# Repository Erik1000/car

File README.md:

# Car

Controlling car functions remotely

This uses an old android phone as hub which connects via BLE to chips controlling functions such as:

- Ignition (remote start, assuming engine immobiliser reports OK)
- windows
- door lock

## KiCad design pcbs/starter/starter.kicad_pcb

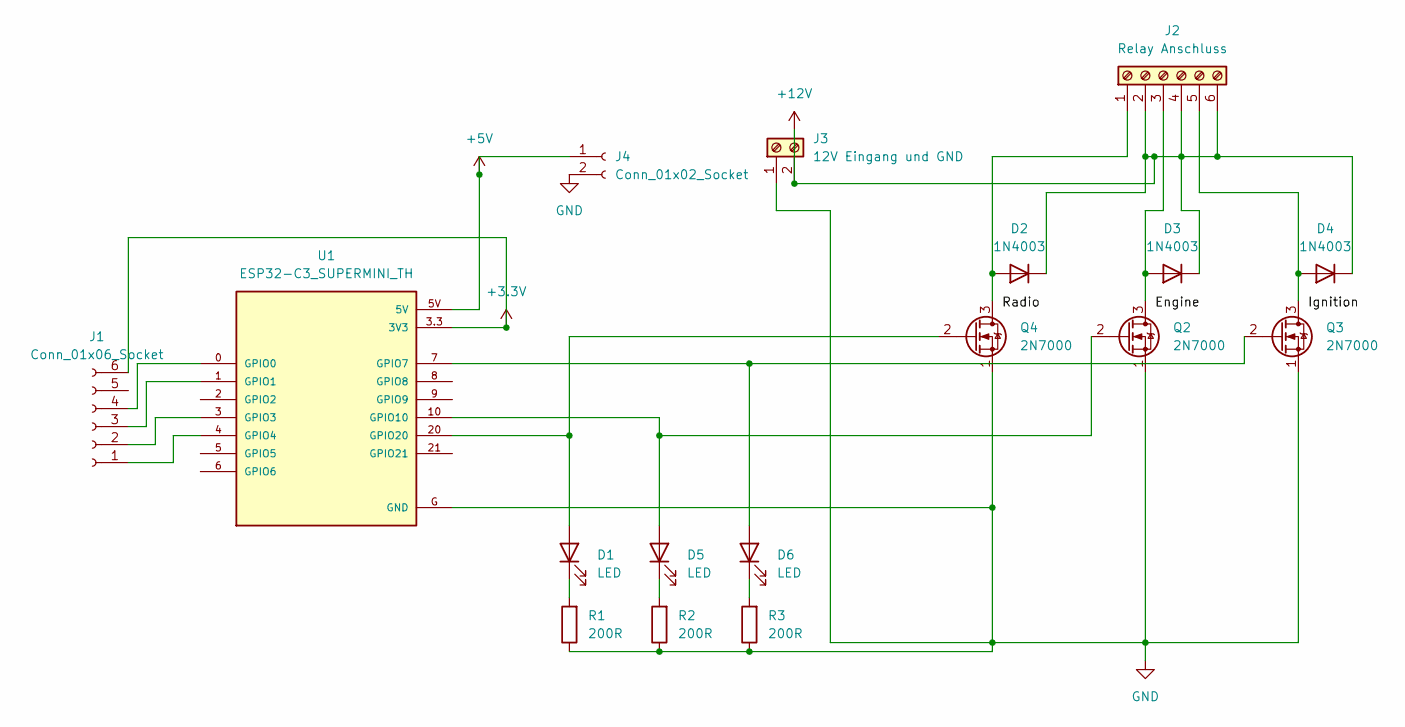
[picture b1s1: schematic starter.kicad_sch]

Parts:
D1, D5, D6: LED; LED_D5.0mm
D2, D3, D4: 1N4003; D_DO-41_SOD81_P10.16mm_Horizontal
J1: Conn_01x06_Socket; JST_XH_B6B-XH-AM_1x06_P2.50mm_Vertical
J2: Relay Anschluss; TerminalBlock_CUI_TB007-508-06_1x06_P5.08mm_Horizontal
J3: 12V Eingang und GND; TerminalBlock_CUI_TB007-508-02_1x02_P5.08mm_Horizontal
J4: Conn_01x02_Socket; JST_XH_B2B-XH-AM_1x02_P2.50mm_Vertical
Q2, Q3, Q4: 2N7000; TO-92_Inline
R1, R2, R3: 200R; R_Axial_DIN0204_L3.6mm_D1.6mm_P5.08mm_Horizontal
U1: ESP32-C3_SUPERMINI_TH; MODULE_ESP32-C3_SUPERMINI

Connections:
+3.3V: J1.6, U1.3.3 (3V3)
+5V: J4.1, U1.5V
+12V: D2.1 (K), D3.1 (K), D4.1 (K), J2.2, J2.4, J2.6, J3.2
GND: J3.1, J4.2, Q2.1 (S), Q3.1 (S), Q4.1 (S), R1.1, R2.1, R3.1, U1.G (GND)
unnamed: D1.2 (A), Q4.2 (G), U1.20 (GPIO20)
unnamed: D1.1 (K), R1.2
unnamed: D2.2 (A), J2.1, Q4.3 (D)
unnamed: D3.2 (A), J2.3, Q2.3 (D)
unnamed: D4.2 (A), J2.5, Q3.3 (D)
unnamed: D5.2 (A), Q2.2 (G), U1.10 (GPIO10)
unnamed: D5.1 (K), R2.2
unnamed: D6.2 (A), Q3.2 (G), U1.7 (GPIO7)
unnamed: D6.1 (K), R3.2
unnamed: J1.1, U1.4 (GPIO4)
unnamed: J1.2, U1.3 (GPIO3)
unnamed: J1.3, U1.1 (GPIO1)
unnamed: J1.4, U1.0 (GPIO0)

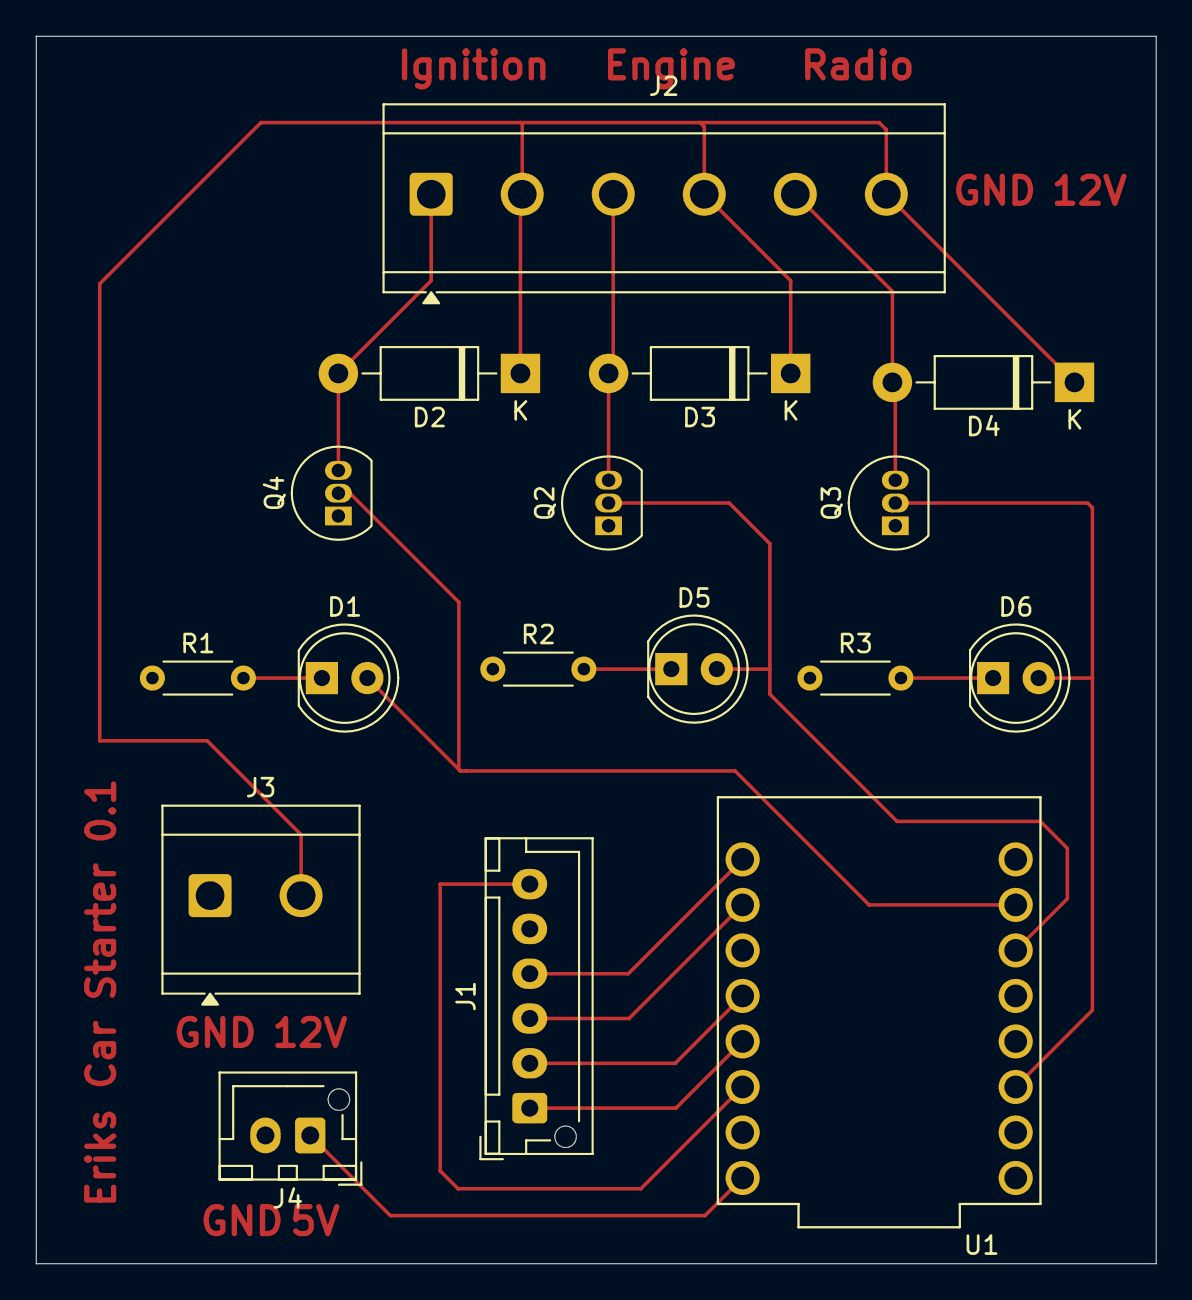
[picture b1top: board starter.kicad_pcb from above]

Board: 2 copper layers, 62.5 x 68.5 mm, 17 parts (0 on the bottom side), 17 nets.

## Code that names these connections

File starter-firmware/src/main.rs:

#![no_std]
#![no_main]

use core::ops::Range;

use bt_hci::controller::ExternalController;
use embassy_embedded_hal::adapter::BlockingAsync;
use embassy_futures::join::join;
use esp_backtrace as _;

use esp_hal::{
    peripherals::{GPIO0, GPIO3, GPIO6},
    rng::Trng,
    timer::{systimer::SystemTimer, timg::TimerGroup},
};
use esp_storage::FlashStorage;
use esp_wifi::ble::controller::BleConnector;
use key::KeyListener;
use relay::RelayHandler;
extern crate alloc;

mod ble;
mod key;
mod relay;
mod schema;

// creds,    data, nvs,     0x110000, 0x2000,
pub const MAP_FLASH_RANGE: Range<u32> = 0x110000..(0x110000 + 0x2000);

#[esp_hal_embassy::main]
async fn main(spawner: embassy_executor::Spawner) {
    esp_backtrace::arch::backtrace();
    let peripherals = esp_hal::init(esp_hal::Config::default());
    esp_alloc::heap_allocator!(size: 72 * 1024);
    esp_println::logger::init_logger_from_env();

    let timg0 = TimerGroup::new(peripherals.TIMG0);
    let trng = Trng::new(peripherals.RNG, peripherals.ADC1);
    let rng = trng.rng;
    let init = esp_wifi::init(timg0.timer0, rng, peripherals.RADIO_CLK).unwrap();

    let systimer = SystemTimer::new(peripherals.SYSTIMER);
    esp_hal_embassy::init(systimer.alarm0);

    let flash = FlashStorage::new();
    let flash = BlockingAsync::new(flash);

    let bluetooth = peripherals.BT;
    let connector = BleConnector::new(&init, bluetooth);
    let controller: ExternalController<_, 20> = ExternalController::new(connector);

    let mut relay_handler = RelayHandler::new(
        peripherals.GPIO10,
        peripherals.GPIO21,
        peripherals.GPIO7,
        peripherals.GPIO20,
    );
    spawner
        .spawn(key_task(
            peripherals.GPIO0,
            peripherals.GPIO3,
            peripherals.GPIO6,
        ))
        .unwrap();

    let (res, _) = join(ble::run(controller, trng, flash), relay_handler.listen()).await;
    if let Err(e) = res {
        log::error!("BLE returned with error: {e:?}");
        panic!("{e:?}")
    }
}

#[embassy_executor::task]
async fn key_task(radio: GPIO0<'static>, engine: GPIO3<'static>, ignition: GPIO6<'static>) {
    let mut key_listener = KeyListener::new(radio, engine, ignition);
    key_listener.listen().await;
}

#[no_mangle]
extern "Rust" fn custom_halt() {
    log::error!("Paniced, resetting...");
    esp_hal::system::software_reset();
}

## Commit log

2023-06-23 added logging
2023-06-23 fixed running service
2023-06-26 added fs monitor
2023-06-26 added fs demo
2023-06-27 refactor library
2023-06-27 added clearLogs button
2023-06-28 cleanup
2023-06-28 mui components
2023-06-29 remove Cargo.lock
2023-06-29 lint fixes
2023-06-29 release fix
2023-06-29 lib update
2023-06-30 README update
2023-07-03 removed jni default-features
2023-07-14 chore: didn't build on opensuse
2023-07-15 ci: Adds docker-compose.yml
2023-07-15 feat: docker compose up almost works
2023-07-15 chore: docker compose up --build shows some more promise
2023-07-15 chore: Needs to set ANDROID_HOME
2023-07-15 feat: docker compose up build the package
2023-07-15 ci: Install tools in container
2023-07-15 doc: docker-compose instruction in README.md and
    Formatting.
2023-07-15 chore: rename image to `subcom/rust_android`
2023-07-15 ci: Use docker-compose to build (closes #1)
2023-07-15 doc: Update to README.md file
2023-07-15 ci: Run container in foreground
2023-07-21 removed vhs config
2024-01-20 Create LICENSE
2024-01-20 ci: Fixes to ci
2024-01-20 chore: Updated tagged image
2024-08-27 change gradle to use python3 not python as command
2024-10-21 init starter firmware
2024-10-23 adjust gpio pins to match pcb
2024-10-23 correctly set gpio pins and change timer to 1 sec ignition
2024-10-29 switch to embassy
2024-10-29 fix typo in Cargo.toml
2024-10-31 physical key overwrites ble state
    ble is still insecure tho
2024-11-16 change package name and set icon
2024-11-19 first working version, very insecure, leaks phone number
2025-04-01 some clean up or so idk old stuff
2025-04-02 add first version for pcb for starter
2025-04-03 first ota draft
2025-04-04 working OTA via wifi ap
2025-04-05 copy ble example
2025-04-05 working draft
2025-04-06 feat: implement ble relay control for door relays and ota enter
2025-04-07 feat: add ble control for everything, timing mut probably adjusted tho
2025-04-09 first pcb revision ordered at JLCPCB
2025-04-09 fix gitignore for kicad
2025-04-09 chore: update to latest trouble-host version
2025-04-16 feat: use "Just Works" BLE encryption which is vulnable to MITM
2025-04-17 fix: adjust for current PCB used in car
2025-04-20 chore: remove unused ble stuff from door controller
2025-04-22 feat: use btleplug for ble instead of android glue code
2025-04-22 fix: do not spawn rustservice in main activity if already running
2025-04-22 fix: check if door controller already found and output discovered services
2025-04-23 chore: rewrite it in rust:tm: to avoid connection/reconnection issues
2025-04-23 fix: do not block on recv for controller because it blocks the queue
2025-04-23 fix: move rest of door controller logic out of if not connected block
2025-04-23 chore: make public
2025-04-24 chore: update gradle stuff, include droidplug as subproject to automatically build it
2025-04-25 remove ota support from android app since it is no longer implemented in door controller firmware
2025-04-25 fix: longer sms now get treated as one sms instead of two
2025-04-26 feat: sms are now signed Json Web Token and authorized phone numbers are controlled by contact "Admin"
2025-04-26 fix: adjust timings to speed things up
2025-04-26 feat: starter ble connection now encrypted
2025-04-26 feat: door controller now supports encryption too but build works only in release
2025-04-27 fix: correctly handle reconnect
2025-05-11 chore: update dependencies and reset on panic instead of halt
2025-05-18 fix: set relay control gpios to pull down and panic if ble returned an error to reset chip
2025-05-18 fix: on panic, reset chip instead of halting
2025-05-27 refactor: use select instad of join to catch methods that returned an error
